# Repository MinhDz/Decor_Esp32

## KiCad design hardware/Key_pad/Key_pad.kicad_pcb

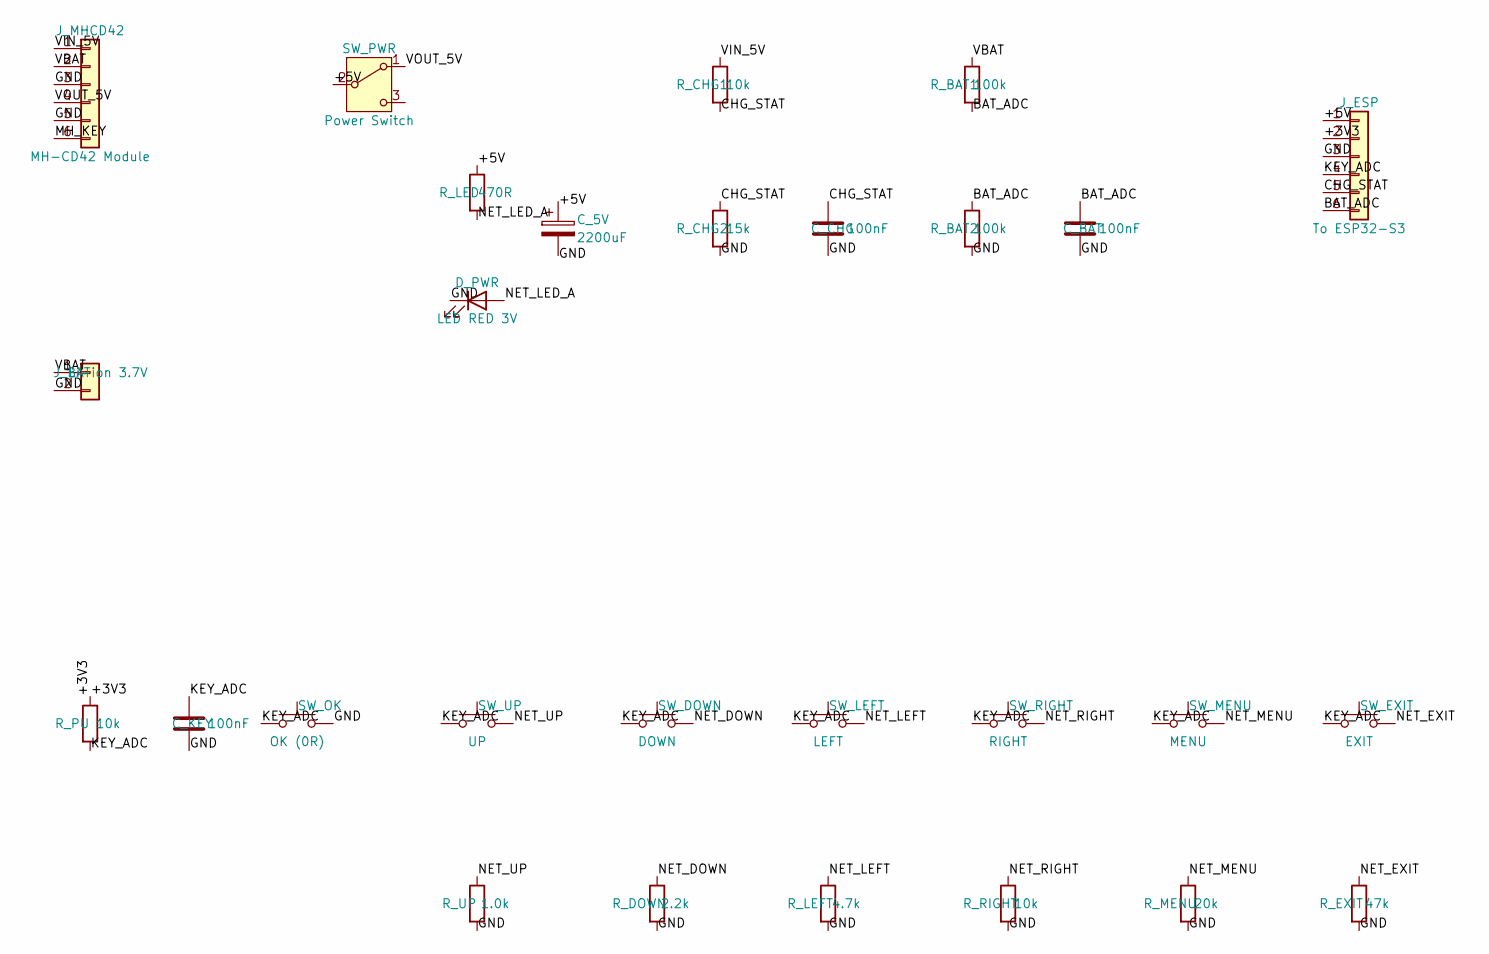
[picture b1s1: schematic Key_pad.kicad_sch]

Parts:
C_5V: 2200uF; CP_Radial_D10.0mm_P5.00mm
C_BAT: 100nF; C_Disc_D5.0mm_W2.5mm_P2.50mm
C_CHG: 100nF; C_Disc_D5.0mm_W2.5mm_P2.50mm
C_KEY: 100nF; C_Disc_D5.0mm_W2.5mm_P2.50mm
D_PWR: LED RED 3V; LED_D3.0mm
J_BAT: Li-ion 3.7V; JST_XH_B2B-XH-A_1x02_P2.50mm_Vertical
J_ESP: To ESP32-S3; PinHeader_1x06_P2.54mm_Vertical
J_MHCD42: MH-CD42 Module; PinHeader_1x06_P2.54mm_Vertical
R_BAT1, R_BAT2: 100k; R_Axial_DIN0207_L6.3mm_D2.5mm_P7.62mm_Horizontal
R_CHG1: 10k; R_Axial_DIN0207_L6.3mm_D2.5mm_P7.62mm_Horizontal
R_CHG2: 15k; R_Axial_DIN0207_L6.3mm_D2.5mm_P7.62mm_Horizontal
R_DOWN: 2.2k; R_Axial_DIN0207_L6.3mm_D2.5mm_P7.62mm_Horizontal
R_EXIT: 47k; R_Axial_DIN0207_L6.3mm_D2.5mm_P7.62mm_Horizontal
R_LED: 470R; R_Axial_DIN0207_L6.3mm_D2.5mm_P7.62mm_Horizontal
R_LEFT: 4.7k; R_Axial_DIN0207_L6.3mm_D2.5mm_P7.62mm_Horizontal
R_MENU: 20k; R_Axial_DIN0207_L6.3mm_D2.5mm_P7.62mm_Horizontal
R_PU: 10k; R_Axial_DIN0207_L6.3mm_D2.5mm_P7.62mm_Horizontal
R_RIGHT: 10k; R_Axial_DIN0207_L6.3mm_D2.5mm_P7.62mm_Horizontal
R_UP: 1.0k; R_Axial_DIN0207_L6.3mm_D2.5mm_P7.62mm_Horizontal
SW_DOWN: DOWN; SW_TactPush_6x6x5mm_2Pin_P4.5mm
SW_EXIT: EXIT; SW_TactPush_6x6x5mm_2Pin_P4.5mm
SW_LEFT: LEFT; SW_TactPush_6x6x5mm_2Pin_P4.5mm
SW_MENU: MENU; SW_TactPush_6x6x5mm_2Pin_P4.5mm
SW_OK: OK (0R); SW_TactPush_6x6x5mm_2Pin_P4.5mm
SW_PWR: Power Switch; SW_Slide_SPDT_Straight_CK_OS102011MS2Q
SW_RIGHT: RIGHT; SW_TactPush_6x6x5mm_2Pin_P4.5mm
SW_UP: UP; SW_TactPush_6x6x5mm_2Pin_P4.5mm

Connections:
+3V3: J_ESP.2, R_PU.1
+5V: C_5V.1, J_ESP.1, R_LED.1, SW_PWR.2 (B)
BAT_ADC: C_BAT.1, J_ESP.6, R_BAT1.2, R_BAT2.1
CHG_STAT: C_CHG.1, J_ESP.5, R_CHG1.2, R_CHG2.1
GND: C_5V.2, C_BAT.2, C_CHG.2, C_KEY.2, D_PWR.1 (K), J_BAT.2, J_ESP.3, J_MHCD42.3, J_MHCD42.5, R_BAT2.2, R_CHG2.2, R_DOWN.2, R_EXIT.2, R_LEFT.2, R_MENU.2, R_RIGHT.2, R_UP.2, SW_OK.2
KEY_ADC: C_KEY.1, J_ESP.4, R_PU.2, SW_DOWN.1, SW_EXIT.1, SW_LEFT.1, SW_MENU.1, SW_OK.1, SW_RIGHT.1, SW_UP.1
MH_KEY: J_MHCD42.6
NET_DOWN: R_DOWN.1, SW_DOWN.2
NET_EXIT: R_EXIT.1, SW_EXIT.2
NET_LED_A: D_PWR.2 (A), R_LED.2
NET_LEFT: R_LEFT.1, SW_LEFT.2
NET_MENU: R_MENU.1, SW_MENU.2
NET_RIGHT: R_RIGHT.1, SW_RIGHT.2
NET_UP: R_UP.1, SW_UP.2
VBAT: J_BAT.1, J_MHCD42.2, R_BAT1.1
VIN_5V: J_MHCD42.1, R_CHG1.1
VOUT_5V: J_MHCD42.4, SW_PWR.1 (A)

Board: 2 copper layers, 32 parts (0 on the bottom side), 16 nets, no tracks yet.

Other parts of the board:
MH1, MH2, MH3, MH4: MountingHole_3.2mm

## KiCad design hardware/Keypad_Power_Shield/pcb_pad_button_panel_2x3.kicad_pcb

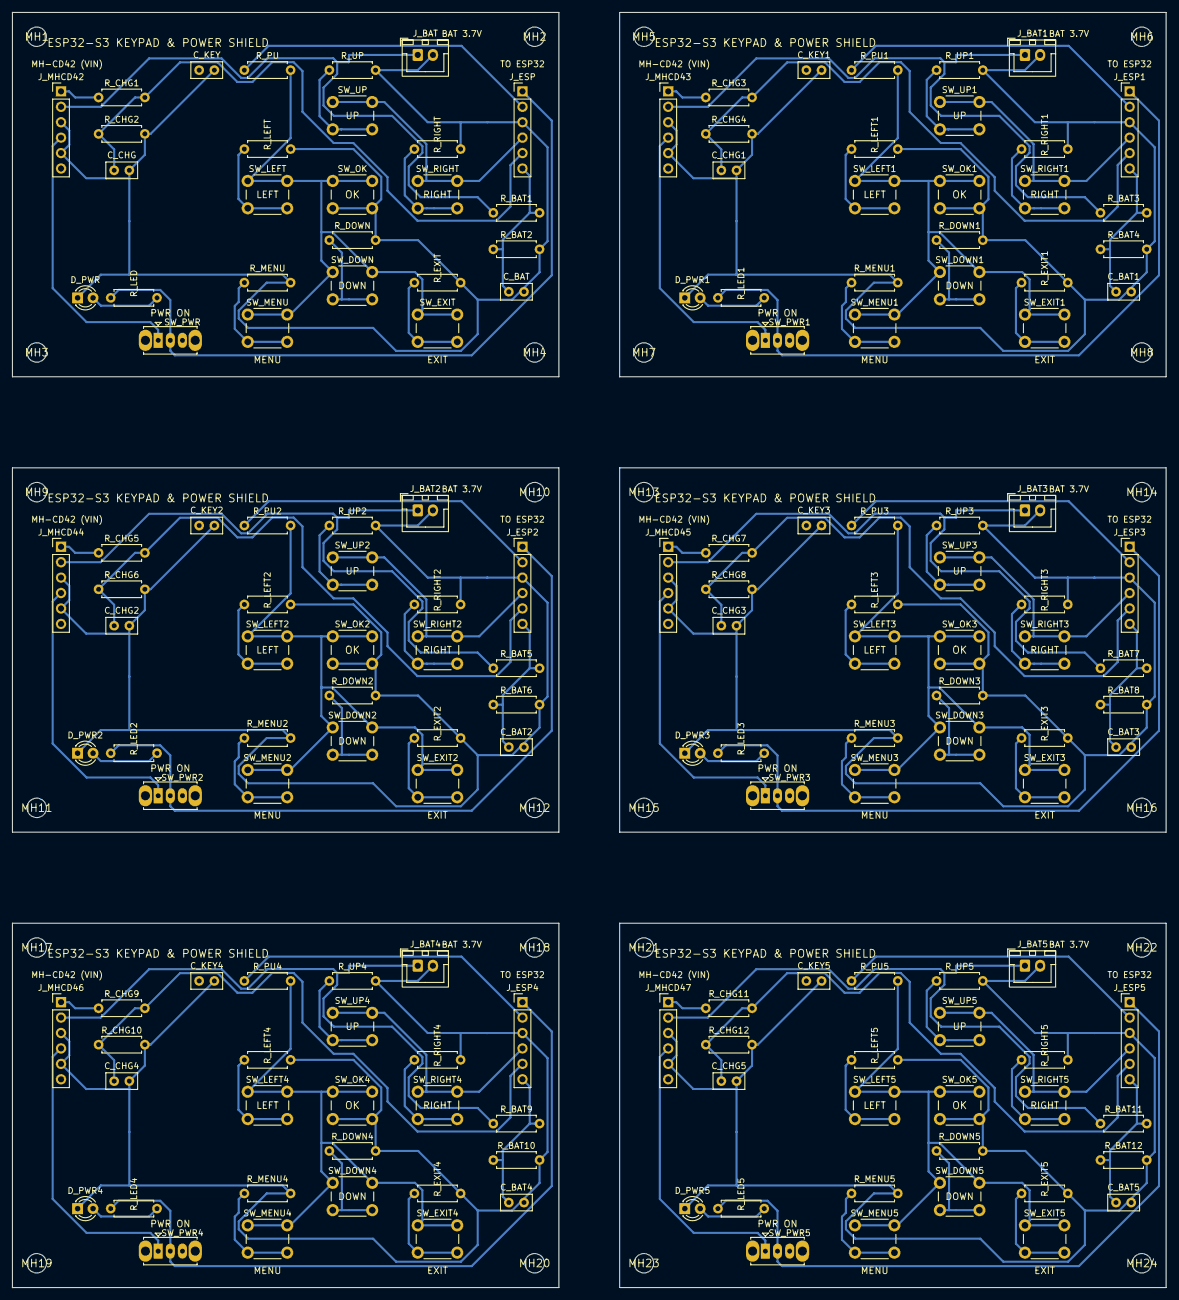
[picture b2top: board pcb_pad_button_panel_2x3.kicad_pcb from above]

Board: 2 copper layers, 190.0 x 210.0 mm, 186 parts (0 on the bottom side), 17 nets.

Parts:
C_BAT, C_BAT1, C_BAT2, C_BAT3, C_BAT4, C_BAT5: 100nF; C_Disc_D5.0mm_W2.5mm_P2.50mm
C_CHG, C_CHG1, C_CHG2, C_CHG3, C_CHG4, C_CHG5: 100nF; C_Disc_D5.0mm_W2.5mm_P2.50mm
C_KEY, C_KEY1, C_KEY2, C_KEY3, C_KEY4, C_KEY5: 100nF; C_Disc_D5.0mm_W2.5mm_P2.50mm
D_PWR, D_PWR1, D_PWR2, D_PWR3, D_PWR4, D_PWR5: LED RED 3V; LED_D3.0mm
J_BAT, J_BAT1, J_BAT2, J_BAT3, J_BAT4, J_BAT5: Li-ion 3.7V; JST_XH_B2B-XH-A_1x02_P2.50mm_Vertical
J_ESP, J_ESP1, J_ESP2, J_ESP3, J_ESP4, J_ESP5: To ESP32-S3; PinHeader_1x06_P2.54mm_Vertical
J_MHCD42, J_MHCD43, J_MHCD44, J_MHCD45, J_MHCD46, J_MHCD47: MH-CD42 Module; PinHeader_1x06_P2.54mm_Vertical
MH1, MH2, MH3, MH4, MH5, MH6, MH7, MH8, MH9, MH10, MH11, MH12, MH13, MH14, MH15, MH16, MH17, MH18, MH19, MH20, MH21, MH22, MH23, MH24: MountingHole_3.2mm
R_BAT1, R_BAT2, R_BAT3, R_BAT4, R_BAT5, R_BAT6, R_BAT7, R_BAT8, R_BAT9, R_BAT10, R_BAT11, R_BAT12: 100k; R_Axial_DIN0207_L6.3mm_D2.5mm_P7.62mm_Horizontal
R_CHG1, R_CHG3, R_CHG5, R_CHG7, R_CHG9, R_CHG11: 10k; R_Axial_DIN0207_L6.3mm_D2.5mm_P7.62mm_Horizontal
R_CHG2, R_CHG4, R_CHG6, R_CHG8, R_CHG10, R_CHG12: 15k; R_Axial_DIN0207_L6.3mm_D2.5mm_P7.62mm_Horizontal
R_DOWN, R_DOWN1, R_DOWN2, R_DOWN3, R_DOWN4, R_DOWN5: 2.2k; R_Axial_DIN0207_L6.3mm_D2.5mm_P7.62mm_Horizontal
R_EXIT, R_EXIT1, R_EXIT2, R_EXIT3, R_EXIT4, R_EXIT5: 47k; R_Axial_DIN0207_L6.3mm_D2.5mm_P7.62mm_Horizontal
R_LED, R_LED1, R_LED2, R_LED3, R_LED4, R_LED5: 470R; R_Axial_DIN0207_L6.3mm_D2.5mm_P7.62mm_Horizontal
R_LEFT, R_LEFT1, R_LEFT2, R_LEFT3, R_LEFT4, R_LEFT5: 4.7k; R_Axial_DIN0207_L6.3mm_D2.5mm_P7.62mm_Horizontal
R_MENU, R_MENU1, R_MENU2, R_MENU3, R_MENU4, R_MENU5: 20k; R_Axial_DIN0207_L6.3mm_D2.5mm_P7.62mm_Horizontal
R_PU, R_PU1, R_PU2, R_PU3, R_PU4, R_PU5: 10k; R_Axial_DIN0207_L6.3mm_D2.5mm_P7.62mm_Horizontal
R_RIGHT, R_RIGHT1, R_RIGHT2, R_RIGHT3, R_RIGHT4, R_RIGHT5: 10k; R_Axial_DIN0207_L6.3mm_D2.5mm_P7.62mm_Horizontal
R_UP, R_UP1, R_UP2, R_UP3, R_UP4, R_UP5: 1.0k; R_Axial_DIN0207_L6.3mm_D2.5mm_P7.62mm_Horizontal
SW_DOWN, SW_DOWN1, SW_DOWN2, SW_DOWN3, SW_DOWN4, SW_DOWN5: DOWN; SW_PUSH_6mm
SW_EXIT, SW_EXIT1, SW_EXIT2, SW_EXIT3, SW_EXIT4, SW_EXIT5: EXIT; SW_PUSH_6mm
SW_LEFT, SW_LEFT1, SW_LEFT2, SW_LEFT3, SW_LEFT4, SW_LEFT5: LEFT; SW_PUSH_6mm
SW_MENU, SW_MENU1, SW_MENU2, SW_MENU3, SW_MENU4, SW_MENU5: MENU; SW_PUSH_6mm
SW_OK, SW_OK1, SW_OK2, SW_OK3, SW_OK4, SW_OK5: OK (0R); SW_PUSH_6mm
SW_PWR, SW_PWR1, SW_PWR2, SW_PWR3, SW_PWR4, SW_PWR5: Power Switch; SW_Slide_SPDT_Straight_CK_OS102011MS2Q
SW_RIGHT, SW_RIGHT1, SW_RIGHT2, SW_RIGHT3, SW_RIGHT4, SW_RIGHT5: RIGHT; SW_PUSH_6mm
SW_UP, SW_UP1, SW_UP2, SW_UP3, SW_UP4, SW_UP5: UP; SW_PUSH_6mm

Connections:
+3V3: J_ESP.2, J_ESP1.2, J_ESP2.2, J_ESP3.2, J_ESP4.2, J_ESP5.2, R_PU.1, R_PU1.1, R_PU2.1, R_PU3.1, R_PU4.1, R_PU5.1
+5V: J_ESP.1, J_ESP1.1, J_ESP2.1, J_ESP3.1, J_ESP4.1, J_ESP5.1, R_LED.1, R_LED1.1, R_LED2.1, R_LED3.1, R_LED4.1, R_LED5.1, SW_PWR.2, SW_PWR1.2, SW_PWR2.2, SW_PWR3.2, SW_PWR4.2, SW_PWR5.2
BAT_ADC: C_BAT.1, C_BAT1.1, C_BAT2.1, C_BAT3.1, C_BAT4.1, C_BAT5.1, J_ESP.6, J_ESP1.6, J_ESP2.6, J_ESP3.6, J_ESP4.6, J_ESP5.6, R_BAT1.2, R_BAT2.1, R_BAT3.2, R_BAT4.1, R_BAT5.2, R_BAT6.1, R_BAT7.2, R_BAT8.1, R_BAT9.2, R_BAT10.1, R_BAT11.2, R_BAT12.1
CHG_STAT: C_CHG.1, C_CHG1.1, C_CHG2.1, C_CHG3.1, C_CHG4.1, C_CHG5.1, J_ESP.5, J_ESP1.5, J_ESP2.5, J_ESP3.5, J_ESP4.5, J_ESP5.5, R_CHG1.2, R_CHG2.1, R_CHG3.2, R_CHG4.1, R_CHG5.2, R_CHG6.1, R_CHG7.2, R_CHG8.1, R_CHG9.2, R_CHG10.1, R_CHG11.2, R_CHG12.1
GND: C_BAT.2, C_BAT1.2, C_BAT2.2, C_BAT3.2, C_BAT4.2, C_BAT5.2, C_CHG.2, C_CHG1.2, C_CHG2.2, C_CHG3.2, C_CHG4.2, C_CHG5.2, C_KEY.2, C_KEY1.2, C_KEY2.2, C_KEY3.2, C_KEY4.2, C_KEY5.2, D_PWR.1, D_PWR1.1, D_PWR2.1, D_PWR3.1, D_PWR4.1, D_PWR5.1, J_BAT.2, J_BAT1.2, J_BAT2.2, J_BAT3.2, J_BAT4.2, J_BAT5.2, J_ESP.3, J_ESP1.3, J_ESP2.3, J_ESP3.3, J_ESP4.3, J_ESP5.3, J_MHCD42.3, J_MHCD42.5, J_MHCD43.3, J_MHCD43.5, J_MHCD44.3, J_MHCD44.5, J_MHCD45.3, J_MHCD45.5, J_MHCD46.3, J_MHCD46.5, J_MHCD47.3, J_MHCD47.5, R_BAT2.2, R_BAT4.2, R_BAT6.2, R_BAT8.2, R_BAT10.2, R_BAT12.2, R_CHG2.2, R_CHG4.2, R_CHG6.2, R_CHG8.2, R_CHG10.2, R_CHG12.2, R_DOWN.2, R_DOWN1.2, R_DOWN2.2, R_DOWN3.2, R_DOWN4.2, R_DOWN5.2, R_EXIT.2, R_EXIT1.2, R_EXIT2.2, R_EXIT3.2, R_EXIT4.2, R_EXIT5.2, R_LEFT.2, R_LEFT1.2, R_LEFT2.2, R_LEFT3.2, R_LEFT4.2, R_LEFT5.2, R_MENU.2, R_MENU1.2, R_MENU2.2, R_MENU3.2, R_MENU4.2, R_MENU5.2, R_RIGHT.2, R_RIGHT1.2, R_RIGHT2.2, R_RIGHT3.2, R_RIGHT4.2, R_RIGHT5.2, R_UP.2, R_UP1.2, R_UP2.2, R_UP3.2, R_UP4.2, R_UP5.2, SW_OK.2, SW_OK1.2, SW_OK2.2, SW_OK3.2, SW_OK4.2, SW_OK5.2
KEY_ADC: C_KEY.1, C_KEY1.1, C_KEY2.1, C_KEY3.1, C_KEY4.1, C_KEY5.1, J_ESP.4, J_ESP1.4, J_ESP2.4, J_ESP3.4, J_ESP4.4, J_ESP5.4, R_PU.2, R_PU1.2, R_PU2.2, R_PU3.2, R_PU4.2, R_PU5.2, SW_DOWN.1, SW_DOWN1.1, SW_DOWN2.1, SW_DOWN3.1, SW_DOWN4.1, SW_DOWN5.1, SW_EXIT.1, SW_EXIT1.1, SW_EXIT2.1, SW_EXIT3.1, SW_EXIT4.1, SW_EXIT5.1, SW_LEFT.1, SW_LEFT1.1, SW_LEFT2.1, SW_LEFT3.1, SW_LEFT4.1, SW_LEFT5.1, SW_MENU.1, SW_MENU1.1, SW_MENU2.1, SW_MENU3.1, SW_MENU4.1, SW_MENU5.1, SW_OK.1, SW_OK1.1, SW_OK2.1, SW_OK3.1, SW_OK4.1, SW_OK5.1, SW_RIGHT.1, SW_RIGHT1.1, SW_RIGHT2.1, SW_RIGHT3.1, SW_RIGHT4.1, SW_RIGHT5.1, SW_UP.1, SW_UP1.1, SW_UP2.1, SW_UP3.1, SW_UP4.1, SW_UP5.1
MH_KEY: J_MHCD42.6, J_MHCD43.6, J_MHCD44.6, J_MHCD45.6, J_MHCD46.6, J_MHCD47.6
NET_DOWN: R_DOWN.1, R_DOWN1.1, R_DOWN2.1, R_DOWN3.1, R_DOWN4.1, R_DOWN5.1, SW_DOWN.2, SW_DOWN1.2, SW_DOWN2.2, SW_DOWN3.2, SW_DOWN4.2, SW_DOWN5.2
NET_EXIT: R_EXIT.1, R_EXIT1.1, R_EXIT2.1, R_EXIT3.1, R_EXIT4.1, R_EXIT5.1, SW_EXIT.2, SW_EXIT1.2, SW_EXIT2.2, SW_EXIT3.2, SW_EXIT4.2, SW_EXIT5.2
NET_LED_A: D_PWR.2, D_PWR1.2, D_PWR2.2, D_PWR3.2, D_PWR4.2, D_PWR5.2, R_LED.2, R_LED1.2, R_LED2.2, R_LED3.2, R_LED4.2, R_LED5.2
NET_LEFT: R_LEFT.1, R_LEFT1.1, R_LEFT2.1, R_LEFT3.1, R_LEFT4.1, R_LEFT5.1, SW_LEFT.2, SW_LEFT1.2, SW_LEFT2.2, SW_LEFT3.2, SW_LEFT4.2, SW_LEFT5.2
NET_MENU: R_MENU.1, R_MENU1.1, R_MENU2.1, R_MENU3.1, R_MENU4.1, R_MENU5.1, SW_MENU.2, SW_MENU1.2, SW_MENU2.2, SW_MENU3.2, SW_MENU4.2, SW_MENU5.2
NET_RIGHT: R_RIGHT.1, R_RIGHT1.1, R_RIGHT2.1, R_RIGHT3.1, R_RIGHT4.1, R_RIGHT5.1, SW_RIGHT.2, SW_RIGHT1.2, SW_RIGHT2.2, SW_RIGHT3.2, SW_RIGHT4.2, SW_RIGHT5.2
NET_UP: R_UP.1, R_UP1.1, R_UP2.1, R_UP3.1, R_UP4.1, R_UP5.1, SW_UP.2, SW_UP1.2, SW_UP2.2, SW_UP3.2, SW_UP4.2, SW_UP5.2
VBAT: J_BAT.1, J_BAT1.1, J_BAT2.1, J_BAT3.1, J_BAT4.1, J_BAT5.1, J_MHCD42.2, J_MHCD43.2, J_MHCD44.2, J_MHCD45.2, J_MHCD46.2, J_MHCD47.2, R_BAT1.1, R_BAT3.1, R_BAT5.1, R_BAT7.1, R_BAT9.1, R_BAT11.1
VIN_5V: J_MHCD42.1, J_MHCD43.1, J_MHCD44.1, J_MHCD45.1, J_MHCD46.1, J_MHCD47.1, R_CHG1.1, R_CHG3.1, R_CHG5.1, R_CHG7.1, R_CHG9.1, R_CHG11.1
VOUT_5V: J_MHCD42.4, J_MHCD43.4, J_MHCD44.4, J_MHCD45.4, J_MHCD46.4, J_MHCD47.4, SW_PWR.1, SW_PWR1.1, SW_PWR2.1, SW_PWR3.1, SW_PWR4.1, SW_PWR5.1
